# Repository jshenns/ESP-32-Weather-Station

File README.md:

# ESP-32-Weather-Station
Weather station that can send data to you via wifi. Meausres temperature, pressure, humidity. Also detects Lightning.

I wanted a weather station that could send data to me over wifi. This is it, it uses a BME-280 Sensor for temperature, pressure, and humidity. It uses an AS3935 Franklin lightning detector and 100nH coil for lightning detection. I initially prototyped it using the Sparkfun breakouts for those sensors, and then integrated everything into a PCB. Whole system centeres around the ESP-32 WROOM 32D module. The Blynk platform is used to stream the data over wifi for now.

Here is the board rendered in Eagle:

Here is the board IRL:

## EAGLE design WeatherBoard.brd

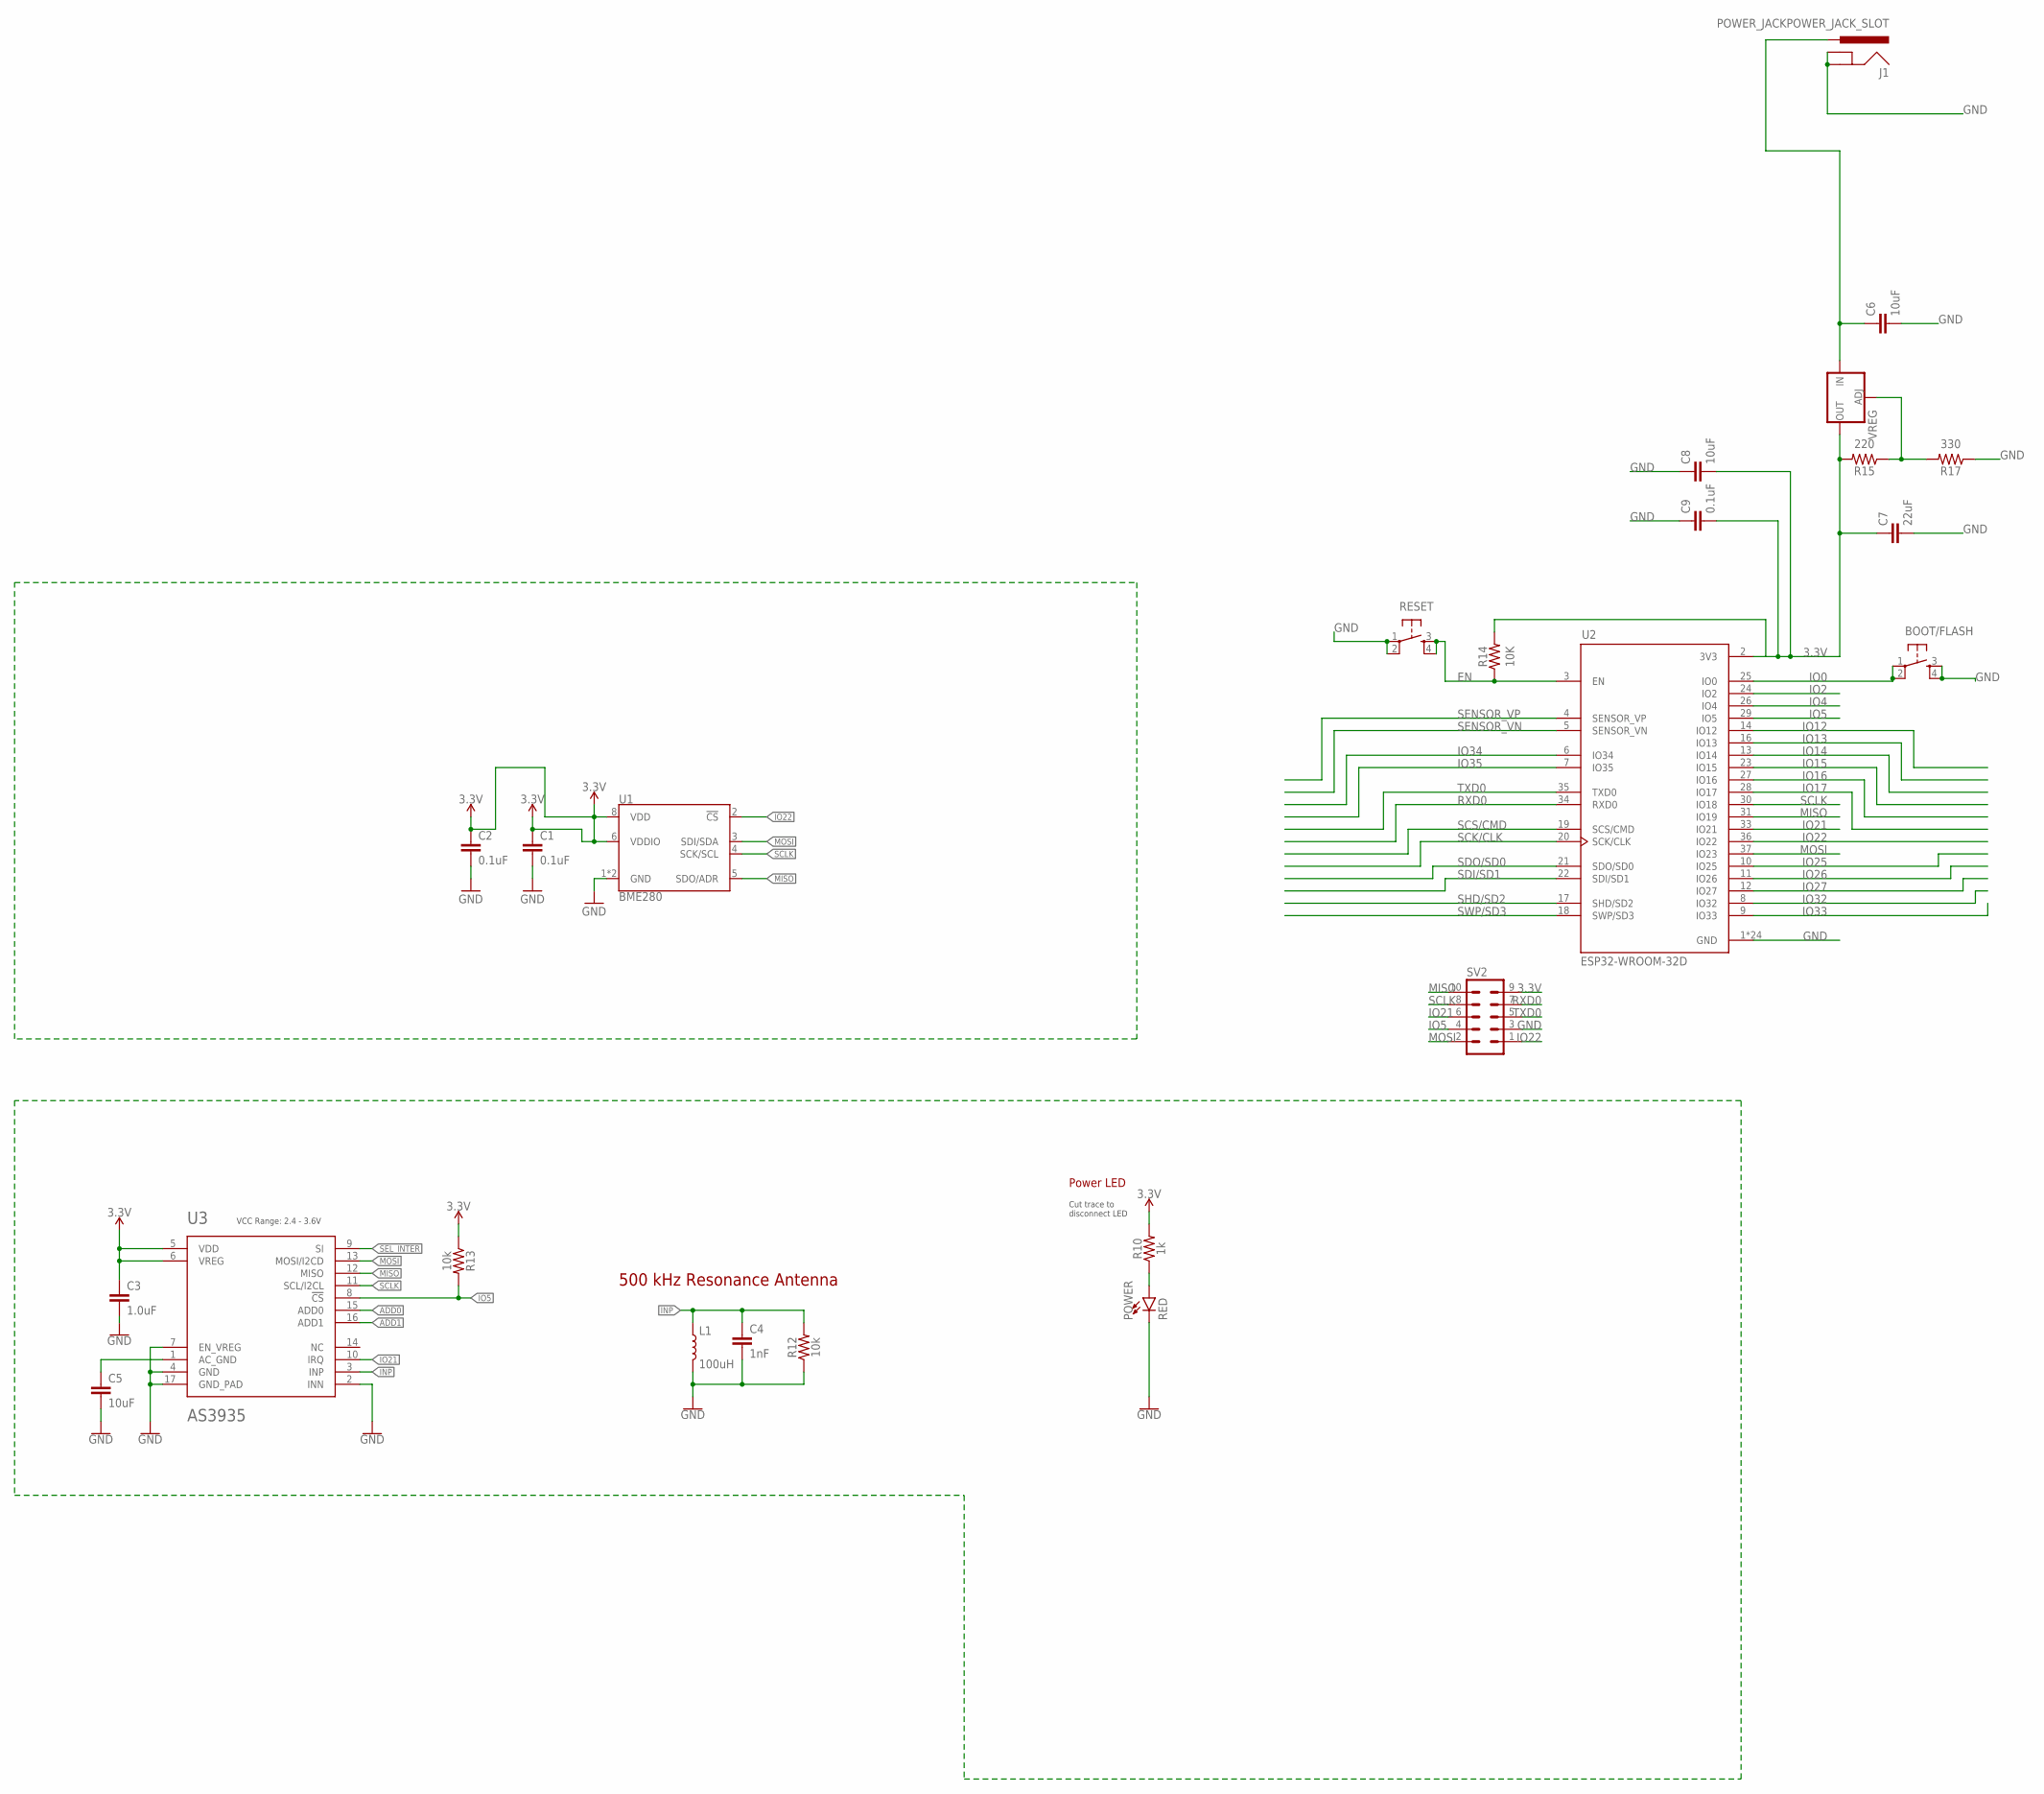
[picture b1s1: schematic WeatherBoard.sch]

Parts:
BOOT/FLASH: TAC_SWITCHPTH; TACTILE-PTH
C1, C2, C9: 0.1uF; 0603
C3: 1.0uF; 0603
C4: 1nF; 0603
C5, C6, C8: 10uF; 0603
C7: 22uF; 0603
J1: POWER_JACKPOWER_JACK_SLOT; POWER_JACK_PTH_SLOT
L1: 100uH; MA5532-AE
POWER: RED; LED-0603
R10: 1k; 0603
R12, R13: 10k; 0603
R14: 10K; 0603
R15: 220; 0603
R17: 330; 0603
RESET: TAC_SWITCHPTH; TACTILE-PTH
SV2: MA05-2
U1: BME280; LGA-8-2.5X2.5
U2: ESP32-WROOM-32D; MODULE_ESP32-WROOM-32D
U3: AS3935; 16LD_MLPQ
VREG: ADJWEATHERSTATION; VREG_NCP1117STAT3G

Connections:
3.3V: C1.1, C2.1, C3.1, C7.1, C8.2, C9.2, R10.2, R13.1, R14.2, R15.2, SV2.9, U1.6 (VDDIO), U1.8 (VDD), U2.2 (3V3), U3.5 (VDD), U3.6 (VREG), VREG.2 (OUT), VREG.4 (OUT)
ADD0: U3.15 (ADD0)
ADD1: U3.16 (ADD1)
EN: R14.1, RESET.3, RESET.4, U2.3 (EN)
GND: BOOT/FLASH.3, BOOT/FLASH.4, C1.2, C2.2, C3.2, C4.2, C5.2, C6.2, C7.2, C8.1, C9.1, J1.GND, J1.GNDBREAK, L1.2, POWER.C, R12.1, R17.1, RESET.1, RESET.2, SV2.3, U1.1 (GND), U1.7 (GND), U2.1 (GND), U2.15 (GND), U2.38 (GND), U2.39_1 (GND), U2.39_2 (GND), U2.39_3 (GND), U2.39_4 (GND), U2.39_5 (GND), U2.39_6 (GND), U2.39_7 (GND), U2.39_8 (GND), U2.39_9 (GND), U2.39_10 (GND), U2.39_11 (GND), U2.39_12 (GND), U2.39_13 (GND), U2.39_14 (GND), U2.39_15 (GND), U2.39_16 (GND), U2.39_17 (GND), U2.39_18 (GND), U2.39_19 (GND), U2.39_20 (GND), U2.39_21 (GND), U3.2 (INN), U3.4 (GND), U3.7 (EN_VREG), U3.17 (GND_PAD)
INP: C4.1, L1.1, R12.2, U3.3 (INP)
IO0: BOOT/FLASH.1, BOOT/FLASH.2, U2.25 (IO0)
IO2: U2.24 (IO2)
IO4: U2.26 (IO4)
IO5: R13.2, SV2.4, U2.29 (IO5), U3.8 (!CS)
IO12: U2.14 (IO12)
IO13: U2.16 (IO13)
IO14: U2.13 (IO14)
IO15: U2.23 (IO15)
IO16: U2.27 (IO16)
IO17: U2.28 (IO17)
IO21: SV2.6, U2.33 (IO21), U3.10 (IRQ)
IO22: SV2.1, U1.2 (!CS), U2.36 (IO22)
IO25: U2.10 (IO25)
IO26: U2.11 (IO26)
IO27: U2.12 (IO27)
IO32: U2.8 (IO32)
IO33: U2.9 (IO33)
IO34: U2.6 (IO34)
IO35: U2.7 (IO35)
MISO: SV2.10, U1.5 (SDO/ADR), U2.31 (IO19), U3.12 (MISO)
MOSI: SV2.2, U1.3 (SDI/SDA), U2.37 (IO23), U3.13 (MOSI/I2CD)
unnamed: C5.1, U3.1 (AC_GND)
unnamed: POWER.A, R10.1
unnamed: R15.1, R17.2, VREG.1 (ADJ)
unnamed: C6.1, J1.PWR, VREG.3 (IN)
RXD0: SV2.7, U2.34 (RXD0)
SCK/CLK: U2.20 (SCK/CLK)
SCLK: SV2.8, U1.4 (SCK/SCL), U2.30 (IO18), U3.11 (SCL/I2CL)
SCS/CMD: U2.19 (SCS/CMD)
SDI/SD1: U2.22 (SDI/SD1)
SDO/SD0: U2.21 (SDO/SD0)
SEL_INTER: U3.9 (SI)
SENSOR_VN: U2.5 (SENSOR_VN)
SENSOR_VP: U2.4 (SENSOR_VP)
SHD/SD2: U2.17 (SHD/SD2)
SWP/SD3: U2.18 (SWP/SD3)
TXD0: SV2.5, U2.35 (TXD0)

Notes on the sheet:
500 kHz Resonance Antenna
VCC Range: 2.4 - 3.6V
Cut trace to disconnect LED
Power LED

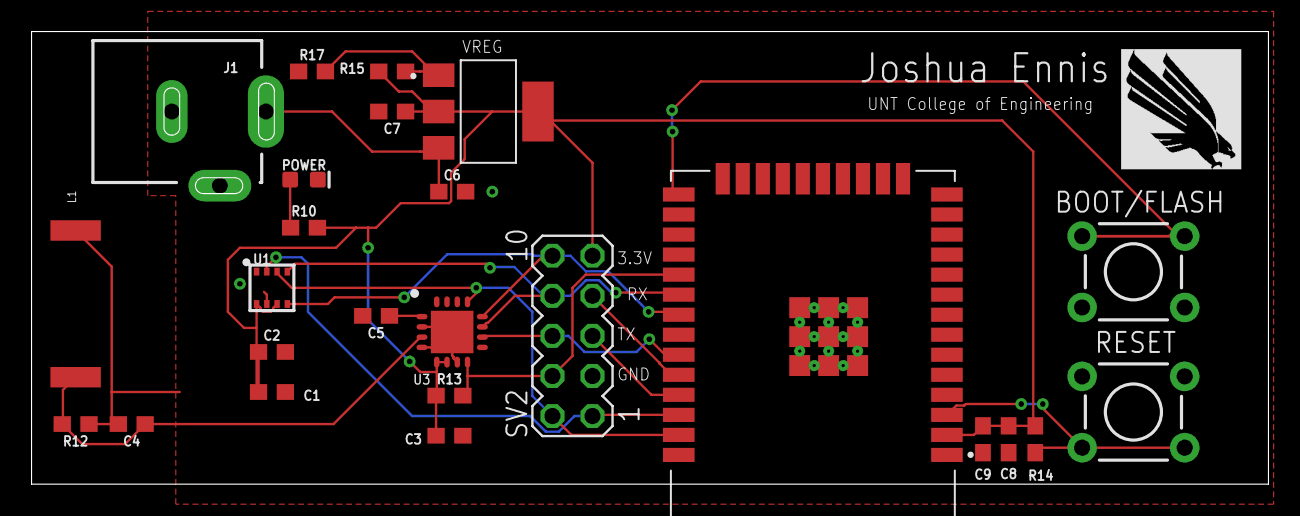
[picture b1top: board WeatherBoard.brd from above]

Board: 2 copper layers, 78.4 x 28.7 mm, 25 parts (0 on the bottom side), 17 nets.

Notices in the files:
parts and their libraries:
SparkFun-Retired: Licensing: Creative Commons ShareAlike 4.0 International - https://creativecommons.org/licenses/by-sa/4.0
SparkFun-Sensors: Licensing: CC v3.0 Share-Alike You are welcome to use this library for commercial purposes.
